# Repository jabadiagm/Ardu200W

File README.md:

# Ardu200W
Convertidor de 200W controlado por arduino

Pensado inicialmente como una fuente de alimentación alimentada con 230V con salida de 12V, 16A, y controlada por un arduino mega. La topología es de medio puente. El arduino programado en C no permite alcanzar una frecuencia aceptable, así que sólo puede ser usado como cargador.

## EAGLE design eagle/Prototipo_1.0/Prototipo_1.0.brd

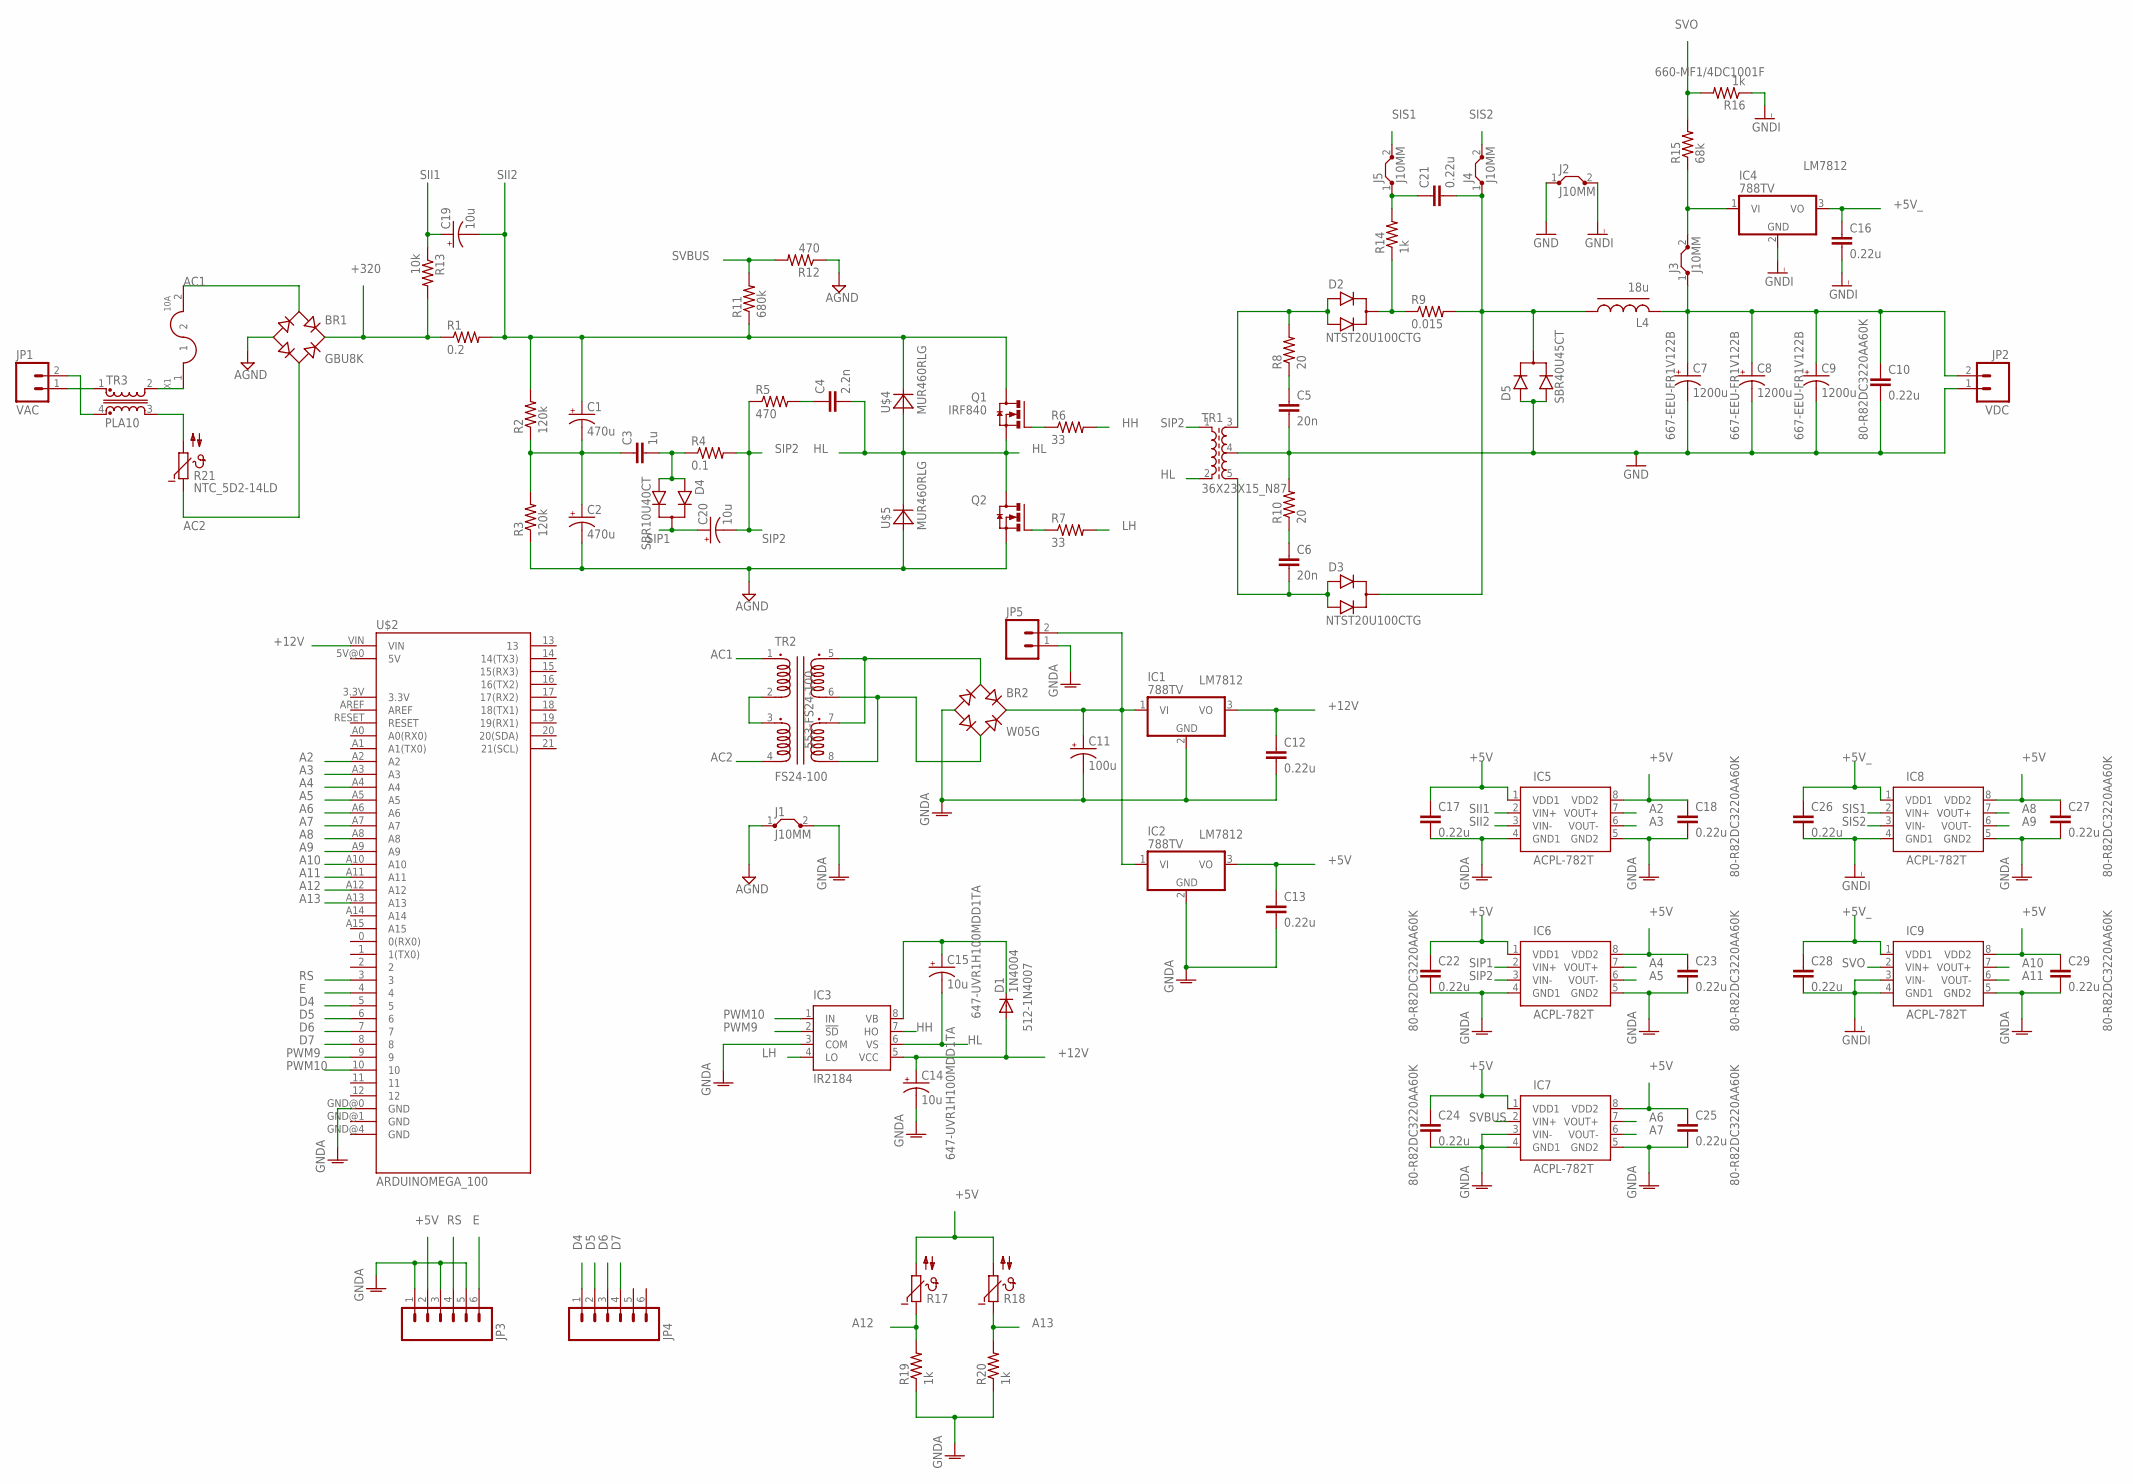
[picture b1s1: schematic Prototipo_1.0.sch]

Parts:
BR1: GBU8K; GBU
BR2: W05G; WOG; MOUSER 625-W06G-E4
C1, C2: 470u; CPOL_RADIAL_470UF_250V
C3: 1u; C22.5B8
C4: 2.2n; C7.5B4
C5, C6: 20n; C10B4; MOUSER 594-S203M75Z5UN63J0R
C7, C8, C9: 1200u; CPOL-RADIAL-1000UF-25V; MOUSER 667-EEU-FR1V122B
C10, C12, C13, C16, C17, C18, C21, C22, C23, C24, C25, C26, C27, C28, C29: 0.22u; C5B3; MOUSER 80-R82DC3220AA60K
C11: 100u; E3,5-8; MOUSER 140-REA101M1HBK0811P
C14, C15, C19, C20: 10u; E2,5-6E; MOUSER 647-UVR1H100MDD1TA
D1: 1N4004; DO41-10; MOUSER 512-1N4007
D2, D3: NTST20U100CTG; TO220V
D4: SBR10U40CT; TO220V
D5: SBR40U45CT; TO220V
IC1: 788TV; TO220V; MOUSER 863-MC7812CTG
IC2, IC4: 788TV; TO220V; MOUSER 863-MC7805CTG
IC3: IR2184; DIL08
IC5, IC6, IC7, IC8, IC9: ACPL-782T; DIL08
J1, J2, J3, J4, J5: J10MM; 10
JP1: VAC; SCREWTERMINAL-3.5MM-2
JP2: VDC; SCREWTERMINAL-5MM-2
JP3, JP4: M06SIP; 1X06
JP5: M02LOCK_LONGPADS; 1X02_LOCK_LONGPADS
L4: 18u; CHOKE_18U
Q1, Q2: IRF840; TO220HV
R1: 0.2; AXIAL-0.6
R2, R3: 120k; AXIAL-0.4; MOUSER 660-MF1/4DCT52R1203F
R4: 0.1; RESISTOR_2W
R5: 470; 0922V
R6, R7: 33; AXIAL-0.5
R8, R10: 20; AXIAL-0.5; MOUSER 603-MFR50SFTE52-20R
R9: 0.015; RSENSE
R11: 680k; AXIAL-0.4; MOUSER 660-MF1/4DC6803F
R12: 470; AXIAL-0.4; MOUSER 660-MF1/4DC4700F
R13: 10k; AXIAL-0.4; MOUSER 660-MF1/4DC1002F
R14, R16, R19, R20: 1k; AXIAL-0.4; MOUSER 660-MF1/4DC1001F
R15: 68k; AXIAL-0.4; MOUSER 660-MF1/4DC6802F
R17, R18: NTC640; P640; MOUSER 594-NTCLE203E3502JB0
R21: NTC_5D2-14LD; C075-042X103
TR1: 36X23X15_N87; CORE_36X23X15
TR2: FS24-100; MOUSER 553-FS24-100
TR3: PLA10; COMMON_MODE_CHOKE_PLA10
U$2: ARDUINOMEGA_100
U$4, U$5: MUR460RLG; CB429-17
X1: 10A; FUSE_HOLDER_5X20

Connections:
$N15: C21.2, D3.2 (C), D5.2 (C), J4.1, L4.1, R9.P$2 (2)
+5V: C13.1, C17.1, C18.1, C22.1, C23.1, C24.1, C25.1, C27.1, C29.1, IC2.3 (VO), IC5.1 (VDD1), IC5.8 (VDD2), IC6.1 (VDD1), IC6.8 (VDD2), IC7.1 (VDD1), IC7.8 (VDD2), IC8.8 (VDD2), IC9.8 (VDD2), JP3.2, R17.2, R18.2
+5V_: C16.1, C26.1, C28.1, IC4.3 (VO), IC8.1 (VDD1), IC9.1 (VDD1)
+12V: C12.1, C14.+, D1.A, IC1.3 (VO), IC3.5 (VCC), U$2.VIN
+320: BR1.4 (+), R1.P$1 (1), R13.P$2 (2)
A2: IC5.7 (VOUT+), U$2.A2
A3: IC5.6 (VOUT-), U$2.A3
A4: IC6.7 (VOUT+), U$2.A4
A5: IC6.6 (VOUT-), U$2.A5
A6: IC7.7 (VOUT+), U$2.A6
A7: IC7.6 (VOUT-), U$2.A7
A8: IC8.7 (VOUT+), U$2.A8
A9: IC8.6 (VOUT-), U$2.A9
A10: IC9.7 (VOUT+), U$2.A10
A11: IC9.6 (VOUT-), U$2.A11
A12: R17.1, R19.P$2 (2), U$2.A12
A13: R18.1, R20.P$2 (2), U$2.A13
AC1: BR1.2 (AC1), TR2.1 (P1.1), X1.2
AC2: BR1.3 (AC2), R21.1, TR2.4 (P2.2)
AGND: BR1.1 (-), C2.2 (-), J1.1, Q2.3 (S), R3.P$1 (1), R12.P$1 (1), U$5.A
D4: JP4.1, U$2.5
D5: JP4.2, U$2.6
D6: JP4.3, U$2.7
D7: JP4.4, U$2.8
E: JP3.6, U$2.4
GND: C5.2, C7.2 (-), C8.2 (-), C9.2 (-), C10.2, D5.1 (A1), D5.3 (A2), J2.1, JP2.1, R10.P$2 (2), TR1.4
GNDA: BR2.-, C11.-, C12.2, C13.2, C14.-, C17.2, C18.2, C22.2, C23.2, C24.2, C25.2, C27.2, C29.2, IC1.2 (GND), IC2.2 (GND), IC3.3 (COM), IC5.4 (GND1), IC5.5 (GND2), IC6.4 (GND1), IC6.5 (GND2), IC7.3 (VIN-), IC7.4 (GND1), IC7.5 (GND2), IC8.5 (GND2), IC9.5 (GND2), J1.2, JP3.1, JP3.3, JP3.5, JP5.1, R19.P$1 (1), R20.P$1 (1), U$2.GND@0 (GND)
GNDI: C16.2, C26.2, C28.2, IC4.2 (GND), IC8.4 (GND1), IC9.3 (VIN-), IC9.4 (GND1), J2.2, R16.P$1 (1)
HH: IC3.7 (HO), R6.P$2 (2)
HL: C4.2, C15.-, IC3.6 (VS), Q1.3 (S), Q2.2 (D), TR1.2, U$4.A, U$5.C
LH: IC3.4 (LO), R7.P$2 (2)
unnamed: TR2.2 (P1.2), TR2.3 (P2.1)
unnamed: R21.2, TR3.3
unnamed: C1.2 (-), C2.1 (+), C3.1, R2.P$1 (1), R3.P$2 (2)
unnamed: IC4.1 (VI), J3.2, R15.P$1 (1)
unnamed: TR3.2, X1.1
unnamed: C3.2, D4.1 (A1), D4.3 (A2), R4.1
unnamed: C4.1, R5.2
unnamed: JP1.1, TR3.1
unnamed: JP1.2, TR3.4
unnamed: Q1.1 (G), R6.P$1 (1)
unnamed: Q2.1 (G), R7.P$1 (1)
unnamed: C5.1, R8.P$1 (1)
unnamed: D2.1 (A1), D2.3 (A2), R8.P$2 (2), TR1.3
unnamed: C7.1 (+), C8.1 (+), C9.1 (+), C10.1, J3.1, JP2.2, L4.2
unnamed: BR2.AC1, TR2.5 (S1.1), TR2.7 (S2.1)
unnamed: D2.2 (C), R9.P$1 (1), R14.P$1 (1)
unnamed: C6.1, R10.P$1 (1)
unnamed: C6.2, D3.1 (A1), D3.3 (A2), TR1.5
unnamed: BR2.AC2, TR2.6 (S1.2), TR2.8 (S2.2)
unnamed: BR2.+, C11.+, IC1.1 (VI), IC2.1 (VI), JP5.2
unnamed: C21.1, J5.1, R14.P$2 (2)
unnamed: C15.+, D1.C, IC3.8 (VB)
PWM9: IC3.2 (!SD), U$2.9
PWM10: IC3.1 (IN), U$2.10
RS: JP3.4, U$2.3
SII1: C19.+, IC5.2 (VIN+), R13.P$1 (1)
SII2: C1.1 (+), C19.-, IC5.3 (VIN-), Q1.2 (D), R1.P$2 (2), R2.P$2 (2), R11.P$1 (1), U$4.C
SIP1: C20.+, D4.2 (C), IC6.2 (VIN+)
SIP2: C20.-, IC6.3 (VIN-), R4.2, R5.1, TR1.1
SIS1: IC8.2 (VIN+), J5.2
SIS2: IC8.3 (VIN-), J4.2
SVBUS: IC7.2 (VIN+), R11.P$2 (2), R12.P$2 (2)
SVO: IC9.2 (VIN+), R15.P$2 (2), R16.P$2 (2)

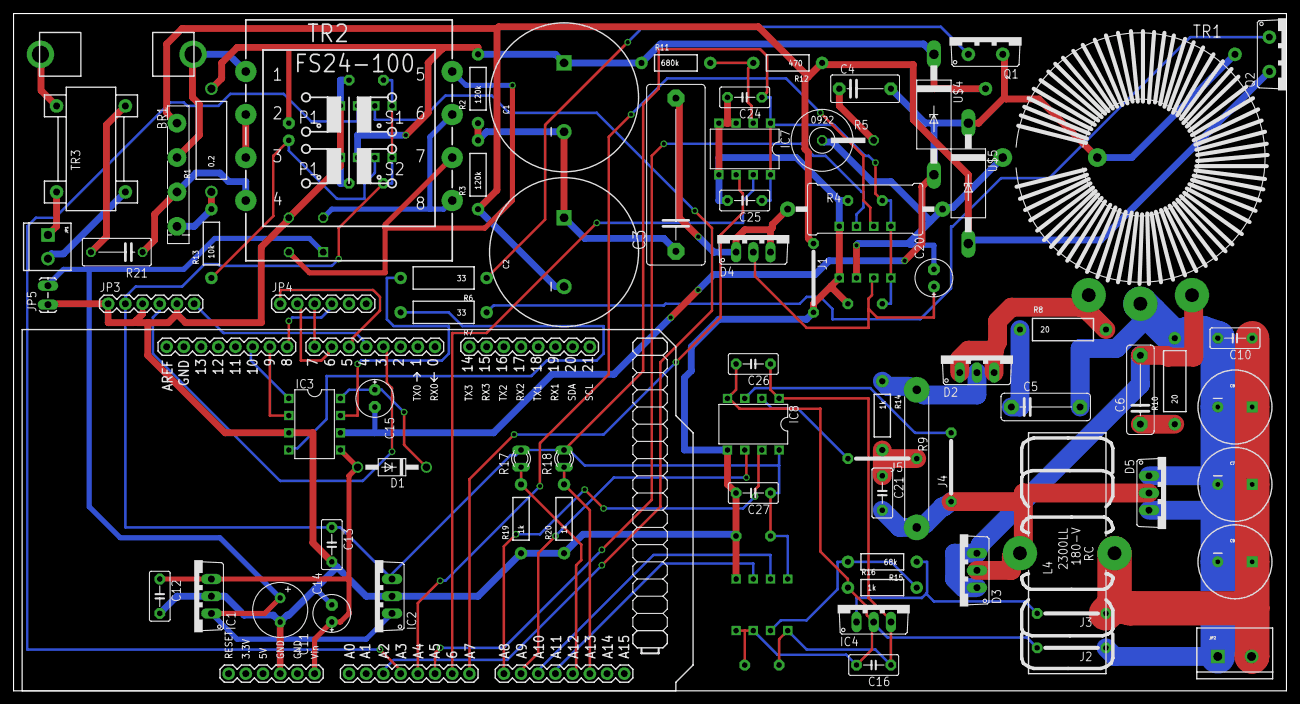
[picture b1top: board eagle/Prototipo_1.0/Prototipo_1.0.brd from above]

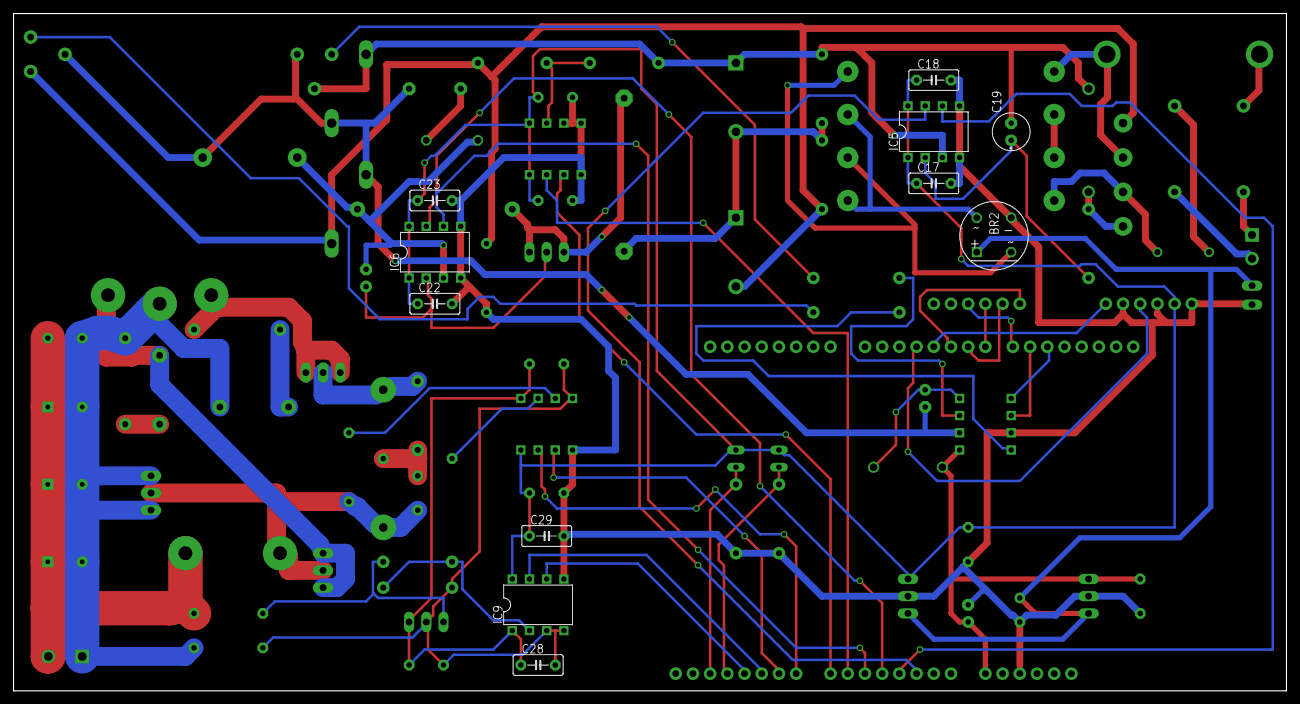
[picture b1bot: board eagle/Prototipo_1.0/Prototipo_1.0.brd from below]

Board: 2 copper layers, 187.9 x 100.0 mm, 86 parts (11 on the bottom side), 64 nets.

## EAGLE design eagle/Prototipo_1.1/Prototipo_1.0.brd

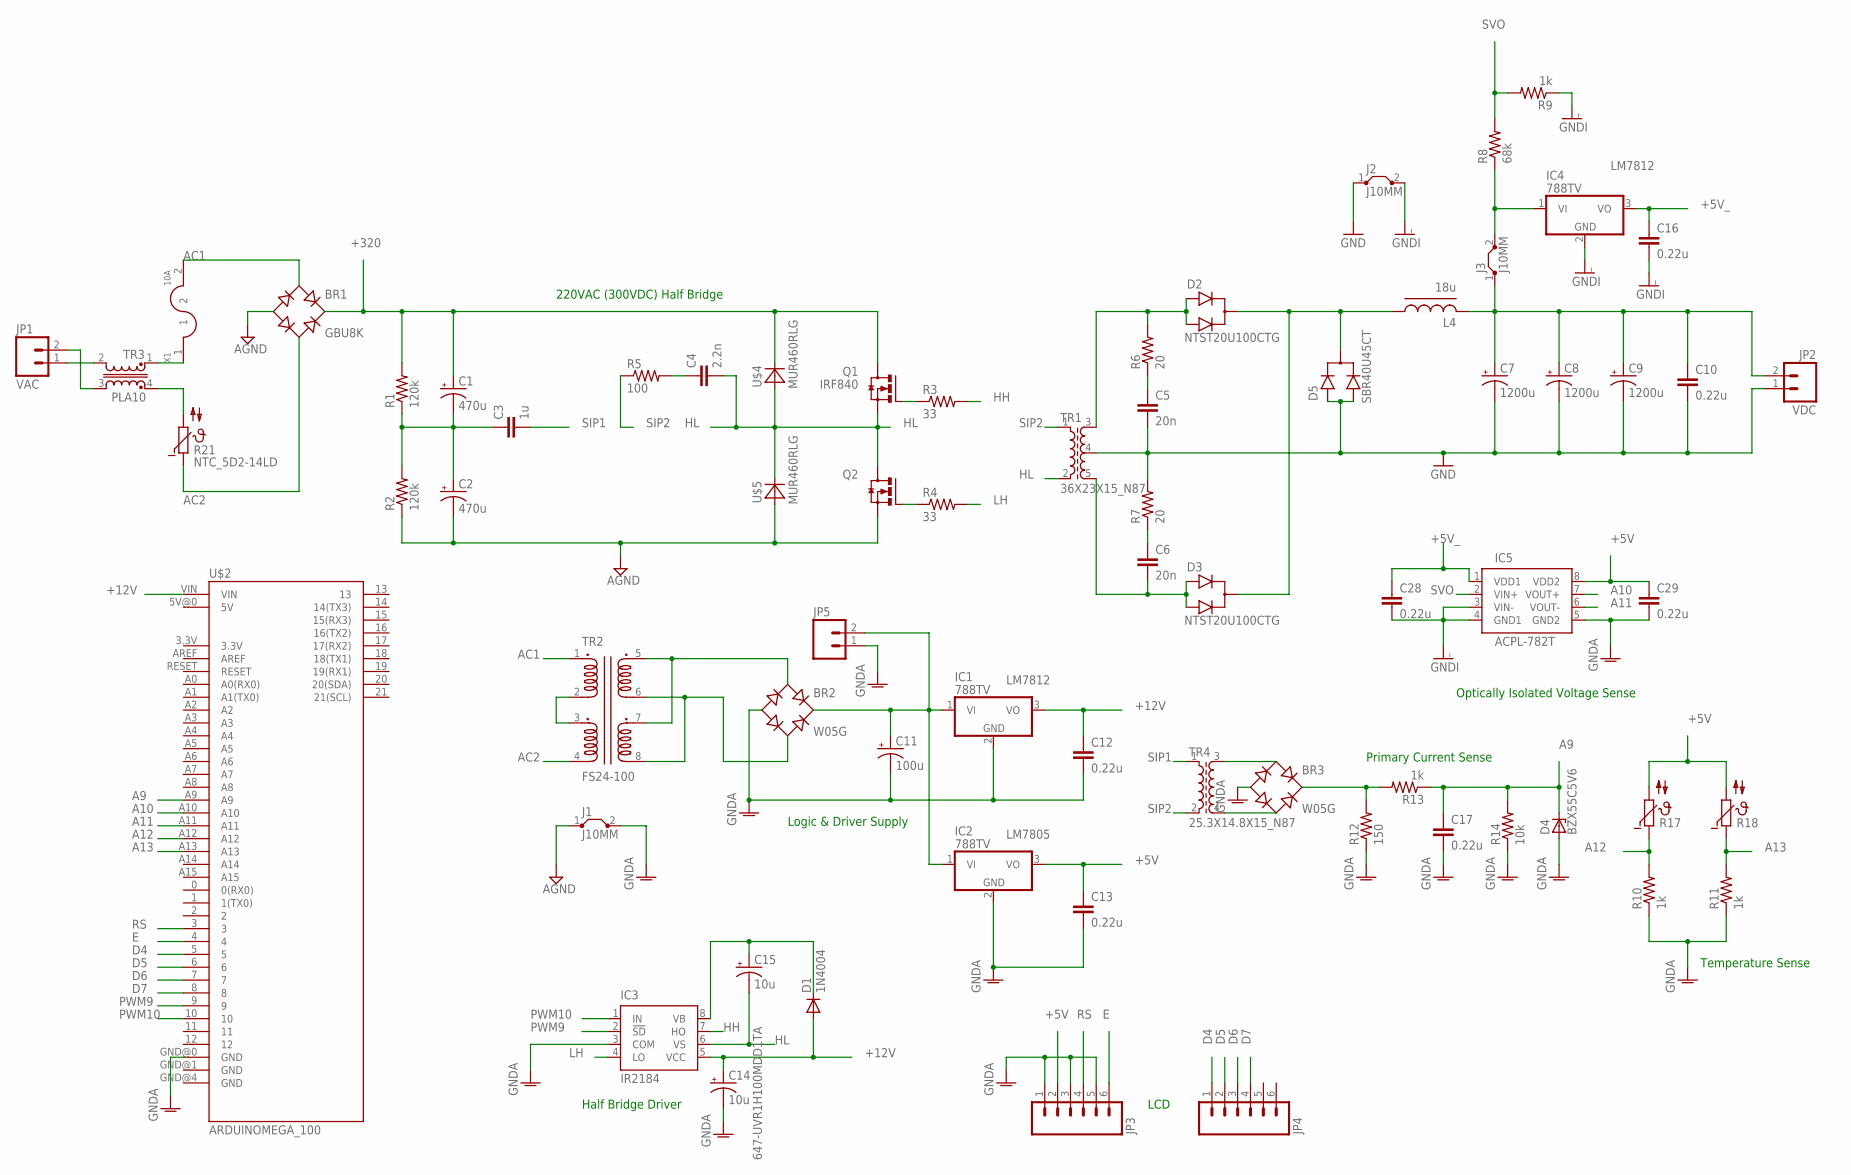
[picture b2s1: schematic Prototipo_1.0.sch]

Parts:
BR1: GBU8K; GBU
BR2: W05G; WOG; MOUSER 625-W06G-E4
BR3: W05G; WOG
C1, C2: 470u; CPOL_RADIAL_470UF_250V
C3: 1u; C22.5B8
C4: 2.2n; C7.5B4
C5, C6: 20n; C10B4; MOUSER 594-S203M75Z5UN63J0R
C7, C8, C9: 1200u; CPOL-RADIAL-1000UF-25V; MOUSER 667-EEU-FR1V122B
C10, C12, C13, C16, C17, C28, C29: 0.22u; C5B3; MOUSER 80-R82DC3220AA60K
C11: 100u; E3,5-8; MOUSER 140-REA101M1HBK0811P
C14, C15: 10u; E2,5-6E; MOUSER 647-UVR1H100MDD1TA
D1: 1N4004; DO41-10; MOUSER 512-1N4007
D2, D3: NTST20U100CTG; TO220V
D4: BZX55C5V6; DO35Z10; MOUSER 78-BZX55C5V6-TAP
D5: SBR40U45CT; TO220V
IC1: 788TV; TO220V; MOUSER 863-MC7812CTG
IC2, IC4: 788TV; TO220V; MOUSER 863-MC7805CTG
IC3: IR2184; DIL08
IC5: ACPL-782T; DIL08
J1, J2, J3: J10MM; 10
JP1: VAC; SCREWTERMINAL-3.5MM-2
JP2: VDC; SCREWTERMINAL-5MM-2
JP3, JP4: M06SIP; 1X06
JP5: M02LOCK_LONGPADS; 1X02_LOCK_LONGPADS
L4: 18u; CHOKE_18U
Q1, Q2: IRF840; TO220HV
R1, R2: 120k; AXIAL-0.4; MOUSER 660-MF1/4DCT52R1203F
R3, R4: 33; AXIAL-0.5
R5: 100; 0922V
R6, R7: 20; AXIAL-0.5; MOUSER 603-MFR50SFTE52-20R
R8: 68k; AXIAL-0.4; MOUSER 660-MF1/4DC6802F
R9, R10, R11, R13: 1k; AXIAL-0.4; MOUSER 660-MF1/4DC1001F
R12: 150; AXIAL-0.4; MOUSER 660-MF1/4DC1500F
R14: 10k; AXIAL-0.4; MOUSER 660-MF1/4DC1002F
R17, R18: NTC640; P640; MOUSER 594-NTCLE203E3502JB0
R21: NTC_5D2-14LD; C075-042X103
TR1: 36X23X15_N87; CORE_36X23X15
TR2: FS24-100; MOUSER 553-FS24-100
TR3: PLA10; COMMON_MODE_CHOKE_PLA10
TR4: 25.3X14.8X15_N87; CORE_25.3X14.8X15
U$2: ARDUINOMEGA_100
U$4, U$5: MUR460RLG; CB429-17
X1: 10A; FUSE_HOLDER_5X20

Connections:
$N15: D2.2 (C), D3.2 (C), D5.2 (C), L4.1
+5V: C13.1, C29.1, IC2.3 (VO), IC5.8 (VDD2), JP3.2, R17.2, R18.2
+5V_: C16.1, C28.1, IC4.3 (VO), IC5.1 (VDD1)
+12V: C12.1, C14.+, D1.A, IC1.3 (VO), IC3.5 (VCC), U$2.VIN
+320: BR1.4 (+), C1.1 (+), Q1.2 (D), R1.P$2 (2), U$4.C
A9: C17.1, D4.C, R13.P$1 (1), R14.P$2 (2), U$2.A9
A10: IC5.7 (VOUT+), U$2.A10
A11: IC5.6 (VOUT-), U$2.A11
A12: R10.P$2 (2), R17.1, U$2.A12
A13: R11.P$2 (2), R18.1, U$2.A13
AC1: BR1.2 (AC1), TR2.1 (P1.1), X1.2
AC2: BR1.3 (AC2), R21.1, TR2.4 (P2.2)
AGND: BR1.1 (-), C2.2 (-), J1.1, Q2.3 (S), R2.P$1 (1), U$5.A
D4: JP4.1, U$2.5
D5: JP4.2, U$2.6
D6: JP4.3, U$2.7
D7: JP4.4, U$2.8
E: JP3.6, U$2.4
GND: C5.2, C7.2 (-), C8.2 (-), C9.2 (-), C10.2, D5.1 (A1), D5.3 (A2), J2.1, JP2.1, R7.P$2 (2), TR1.4
GNDA: BR2.-, BR3.-, C11.-, C12.2, C13.2, C14.-, C17.2, C29.2, D4.A, IC1.2 (GND), IC2.2 (GND), IC3.3 (COM), IC5.5 (GND2), J1.2, JP3.1, JP3.3, JP3.5, JP5.1, R10.P$1 (1), R11.P$1 (1), R12.P$1 (1), R14.P$1 (1), U$2.GND@0 (GND)
GNDI: C16.2, C28.2, IC4.2 (GND), IC5.3 (VIN-), IC5.4 (GND1), J2.2, R9.P$1 (1)
HH: IC3.7 (HO), R3.P$2 (2)
HL: C4.2, C15.-, IC3.6 (VS), Q1.3 (S), Q2.2 (D), TR1.2, U$4.A, U$5.C
LH: IC3.4 (LO), R4.P$2 (2)
unnamed: TR2.2 (P1.2), TR2.3 (P2.1)
unnamed: R21.2, TR3.4
unnamed: C1.2 (-), C2.1 (+), C3.1, R1.P$1 (1), R2.P$2 (2)
unnamed: IC4.1 (VI), J3.2, R8.P$1 (1)
unnamed: TR3.1, X1.1
unnamed: BR3.AC1, TR4.3
unnamed: C4.1, R5.2
unnamed: JP1.1, TR3.2
unnamed: JP1.2, TR3.3
unnamed: Q1.1 (G), R3.P$1 (1)
unnamed: Q2.1 (G), R4.P$1 (1)
unnamed: C5.1, R6.P$1 (1)
unnamed: D2.1 (A1), D2.3 (A2), R6.P$2 (2), TR1.3
unnamed: C7.1 (+), C8.1 (+), C9.1 (+), C10.1, J3.1, JP2.2, L4.2
unnamed: BR2.AC1, TR2.5 (S1.1), TR2.7 (S2.1)
unnamed: BR3.AC2, TR4.4
unnamed: C6.1, R7.P$1 (1)
unnamed: BR3.+, R12.P$2 (2), R13.P$2 (2)
unnamed: C6.2, D3.1 (A1), D3.3 (A2), TR1.5
unnamed: BR2.AC2, TR2.6 (S1.2), TR2.8 (S2.2)
unnamed: BR2.+, C11.+, IC1.1 (VI), IC2.1 (VI), JP5.2
unnamed: C15.+, D1.C, IC3.8 (VB)
PWM9: IC3.2 (!SD), U$2.9
PWM10: IC3.1 (IN), U$2.10
RS: JP3.4, U$2.3
SIP1: C3.2, TR4.1
SIP2: R5.1, TR1.1, TR4.2
SVO: IC5.2 (VIN+), R8.P$2 (2), R9.P$2 (2)

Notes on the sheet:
Half Bridge Driver
220VAC (300VDC) Half Bridge
Optically Isolated Voltage Sense
Primary Current Sense
Temperature Sense
LCD
Logic & Driver Supply

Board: 2 copper layers, 68 parts (4 on the bottom side), 52 nets, no tracks yet.

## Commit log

2020-06-08 primer commit

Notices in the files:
parts and their libraries:
SparkFun-Passives: Licensing: CC v3.0 Share-Alike You are welcome to use this library for commercial purposes.
